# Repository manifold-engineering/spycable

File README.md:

# Manifold Spycable  
**_Work in Progress_**

**Manifold Spycable** is a project that aims to explore the boundaries of miniaturized embedded electronics by integrating a fully functional computer within a standard XLR connector. 

---

## Overview  
The Manifold Spycable comprises several components:

### 1. **The Spycable Device**  
- A single PCB computer designed to fit inside a standard XLR connector (such as the Neutrik NC3MMX or similar) - similar form factor as [Manifold PAT-MAT](https://github.com/manifold-engineering/pat-mat)
- Powered directly from standard 48V phantom power, commonly used in professional audio equipment.  
- Equipped with:  
  - **TI PCM1820/1821/1822 ADC** for audio data conversion.  
  - **ESP8685 MCU** based on the RISC-V ESP32-C3 core with Wi-Fi capability.  
- Features a **u.FL IPEX connector** for a Wi-Fi antenna. A detailed evaluation of compatible antennas (e.g., Fractus Compact Reach Xtend with coax cable) will be added later.  
- Designed to allow space for a microphone cable to pass through, enabling the creation of standard-looking XLR cables capable of audio data transmission and recording.

### 2. **Firmware**  
Custom firmware for the ESP8685 to handle audio data acquisition from the ADC and real-time data transmission over Wi-Fi.

### 3. **Receiver Software**  
Software for standaerd computer systems to process the incoming audio data streams. Possible functions might include audio file recording and real-time playback.

---
### Development Stage  
This project is in its **early development stage**. Currently, only the hardware design for the device is ready. Firmware and receiver software development are still in progress.

**Note**: This project may have potential data security implications if used in unintended ways. However, it is intended purely for educational, experimental, and demonstration purposes.  

---

## Licensing  
This project is licensed under the **MIT License**. See the `LICENSE` file for more information.

---

## Future Development  
Stay tuned for:  
- Firmware updates for the embedded ESP8685.  
- Antenna recommendations and performance benchmarks.  
- Receiver software to enable audio recording and playback.

---

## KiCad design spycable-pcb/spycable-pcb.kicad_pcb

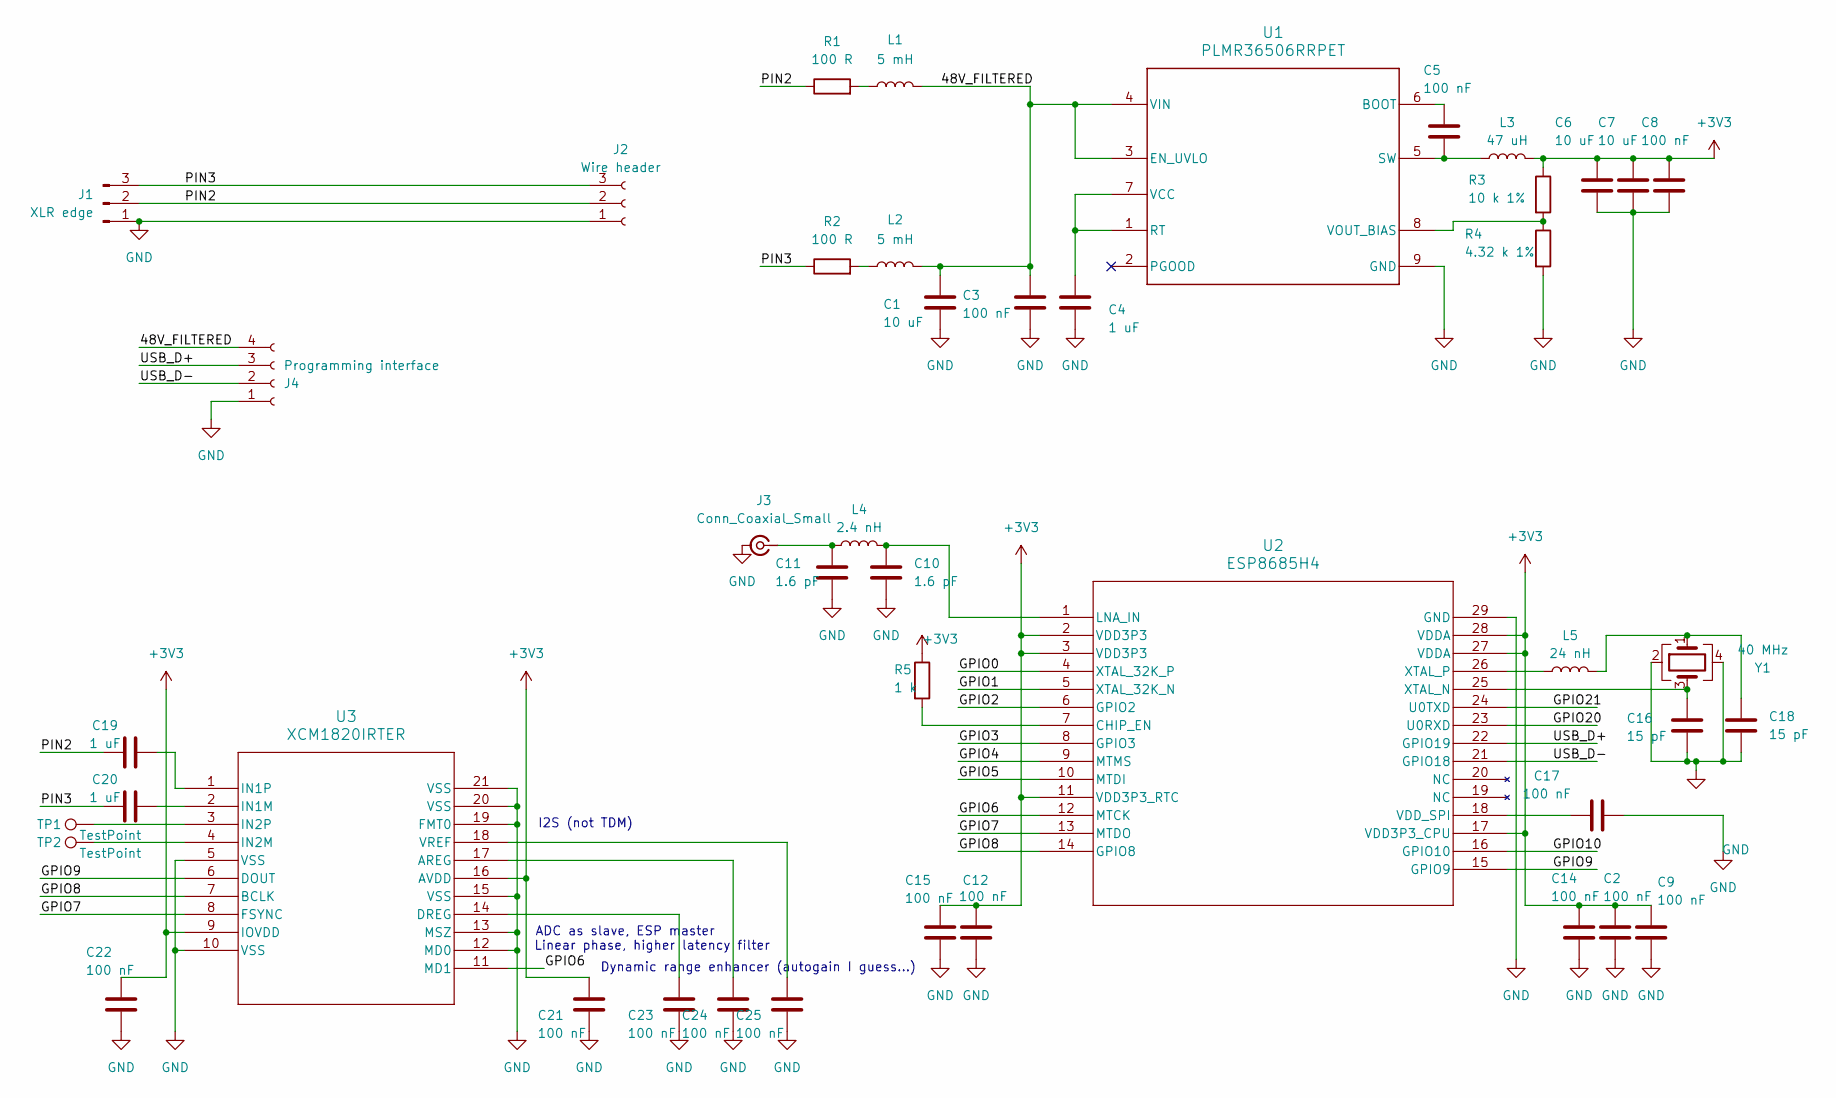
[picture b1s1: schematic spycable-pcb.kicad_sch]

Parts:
C1: 10 uF; C_1206_3216Metric
C2, C5, C9, C12, C14, C15, C17, C21, C22, C23, C24, C25: 100 nF; C_0402_1005Metric
C3, C8: 100 nF; C_0603_1608Metric
C4, C19, C20: 1 uF; C_0402_1005Metric
C6, C7: 10 uF; C_0603_1608Metric
C10, C11: 1.6 pF; C_0201_0603Metric
C16, C18: 15 pF; C_0402_1005Metric
J1: XLR edge; XLR_PCB
J2: Wire header; PinHeader_1x03_P2.54mm_Vertical
J3: Conn_Coaxial_Small; U.FL_Hirose_U.FL-R-SMT-1_Vertical
J4: Programming interface; USB pogo pads
L1, L2: 5 mH; L_Changjiang_FNR5040S
L3: 47 uH; L_Changjiang_FNR4030S
L4: 2.4 nH; L_0201_0603Metric
L5: 24 nH; L_0402_1005Metric
R1, R2: 100 R; R_0603_1608Metric
R3: 10 k 1%; R_0402_1005Metric
R4: 4.32 k 1%; R_0402_1005Metric
R5: 1 k; R_0402_1005Metric
TP1, TP2: TestPoint; TestPoint_Pad_D1.0mm
U1: PLMR36506RRPET; RPE0009A-MFG
U2: ESP8685H4; QFN284X4_EXP
U3: XCM1820IRTER; QFN_820IRTER_TEX
Y1: 40 MHz; Crystal_SMD_2016-4Pin_2.0x1.6mm

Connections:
+3V3: C2.1, C6.1, C7.1, C8.1, C9.1, C12.2, C14.1, C15.2, C21.2, C22.2, L3.2, R3.1, R5.1, U2.2 (VDD3P3), U2.3 (VDD3P3), U2.11 (VDD3P3_RTC), U2.17 (VDD3P3_CPU), U2.27 (VDDA), U2.28 (VDDA), U3.9 (IOVDD), U3.16 (AVDD)
/48V_FILTERED: C1.2, C3.1, J4.4, L1.2, L2.2, U1.3 (EN_UVLO), U1.4 (VIN)
/GPIO0: U2.4 (XTAL_32K_P)
/GPIO1: U2.5 (XTAL_32K_N)
/GPIO2: U2.6 (GPIO2)
/GPIO3: U2.8 (GPIO3)
/GPIO4: U2.9 (MTMS)
/GPIO5: U2.10 (MTDI)
/GPIO6: U2.12 (MTCK), U3.11 (MD1)
/GPIO7: U2.13 (MTDO), U3.8 (FSYNC)
/GPIO8: U2.14 (GPIO8), U3.7 (BCLK)
/GPIO9: U2.15 (GPIO9), U3.6 (DOUT)
/GPIO10: U2.16 (GPIO10)
/GPIO20: U2.23 (U0RXD)
/GPIO21: U2.24 (U0TXD)
/PIN2: C19.1, J1.2, J2.2, R1.1
/PIN3: C20.1, J1.3, J2.3, R2.1
/USB_D+: J4.3, U2.22 (GPIO19)
/USB_D-: J4.2, U2.21 (GPIO18)
GND: C1.1, C2.2, C3.2, C4.2, C6.2, C7.2, C8.2, C9.2, C10.1, C11.2, C12.1, C14.2, C15.1, C16.2, C17.2, C18.2, C21.1, C22.1, C23.1, C24.1, C25.1, J1.1, J2.1, J3.2 (Ext), J4.1, R4.2, U1.9 (GND), U2.29 (GND), U3.5 (VSS), U3.10 (VSS), U3.12 (MD0), U3.13 (MSZ), U3.15 (VSS), U3.19 (FMT0), U3.20 (VSS), U3.21 (VSS), Y1.2, Y1.4
unnamed: C18.1, L5.2, Y1.1
unnamed: C11.1, J3.1 (In), L4.1
unnamed: L1.1, R1.2
unnamed: L2.1, R2.2
unnamed: C5.1, U1.6 (BOOT)
unnamed: C4.1, U1.1 (RT), U1.7 (VCC)
unnamed: C5.2, L3.1, U1.5 (SW)
unnamed: R3.2, R4.1, U1.8 (VOUT_BIAS)
unnamed: R5.2, U2.7 (CHIP_EN)
unnamed: C10.2, L4.2, U2.1 (LNA_IN)
unnamed: C17.1, U2.18 (VDD_SPI)
unnamed: C16.1, U2.25 (XTAL_N), Y1.3
unnamed: L5.1, U2.26 (XTAL_P)
unnamed: C24.2, U3.17 (AREG)
unnamed: C23.2, U3.14 (DREG)
unnamed: C20.2, U3.2 (IN1M)
unnamed: C19.2, U3.1 (IN1P)
unnamed: TP2.1, U3.4 (IN2M)
unnamed: TP1.1, U3.3 (IN2P)
unnamed: C25.2, U3.18 (VREF)

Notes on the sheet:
I2S (not TDM)
ADC as slave, ESP master
Dynamic range enhancer (autogain I guess...)
Linear phase, higher latency filter

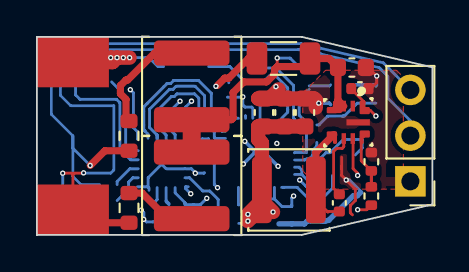
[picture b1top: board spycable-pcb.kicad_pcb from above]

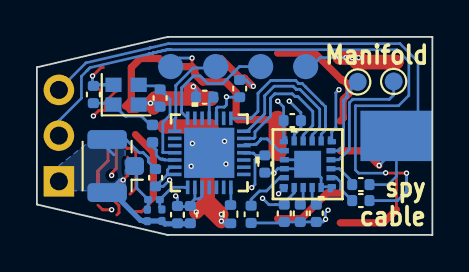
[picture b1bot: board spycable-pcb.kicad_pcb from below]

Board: 4 copper layers, 22.0 x 11.0 mm, 44 parts (27 on the bottom side), 31 nets.

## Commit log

2025-03-26 Initial commit, first hardware revision seems done
2025-03-26 Licence and tentative readme
2025-03-26 readme fix
2025-05-05 first try on reciever
2025-05-09 Basic structure for simple core ringbuffer maybe ready
2025-05-11 basic network ingest protoype
2025-05-14 Including portaudio sources
2025-05-19 Rewriting from scratch for the third time
2025-05-19 Data insertion WiP, now metadata in sparse tree struct, audio sample not ready yet
2025-05-26 Preliminary implementation and trest of audio buffer data atructure
2025-05-28 buffer ingestion seems preliminary tested and fixed
2025-06-02 minor buffer readout fixes
2025-06-21 Deinterlacing and data padding preliminary done, not tested yet
2025-06-22 preliminary network data ingest in RTP test v3
